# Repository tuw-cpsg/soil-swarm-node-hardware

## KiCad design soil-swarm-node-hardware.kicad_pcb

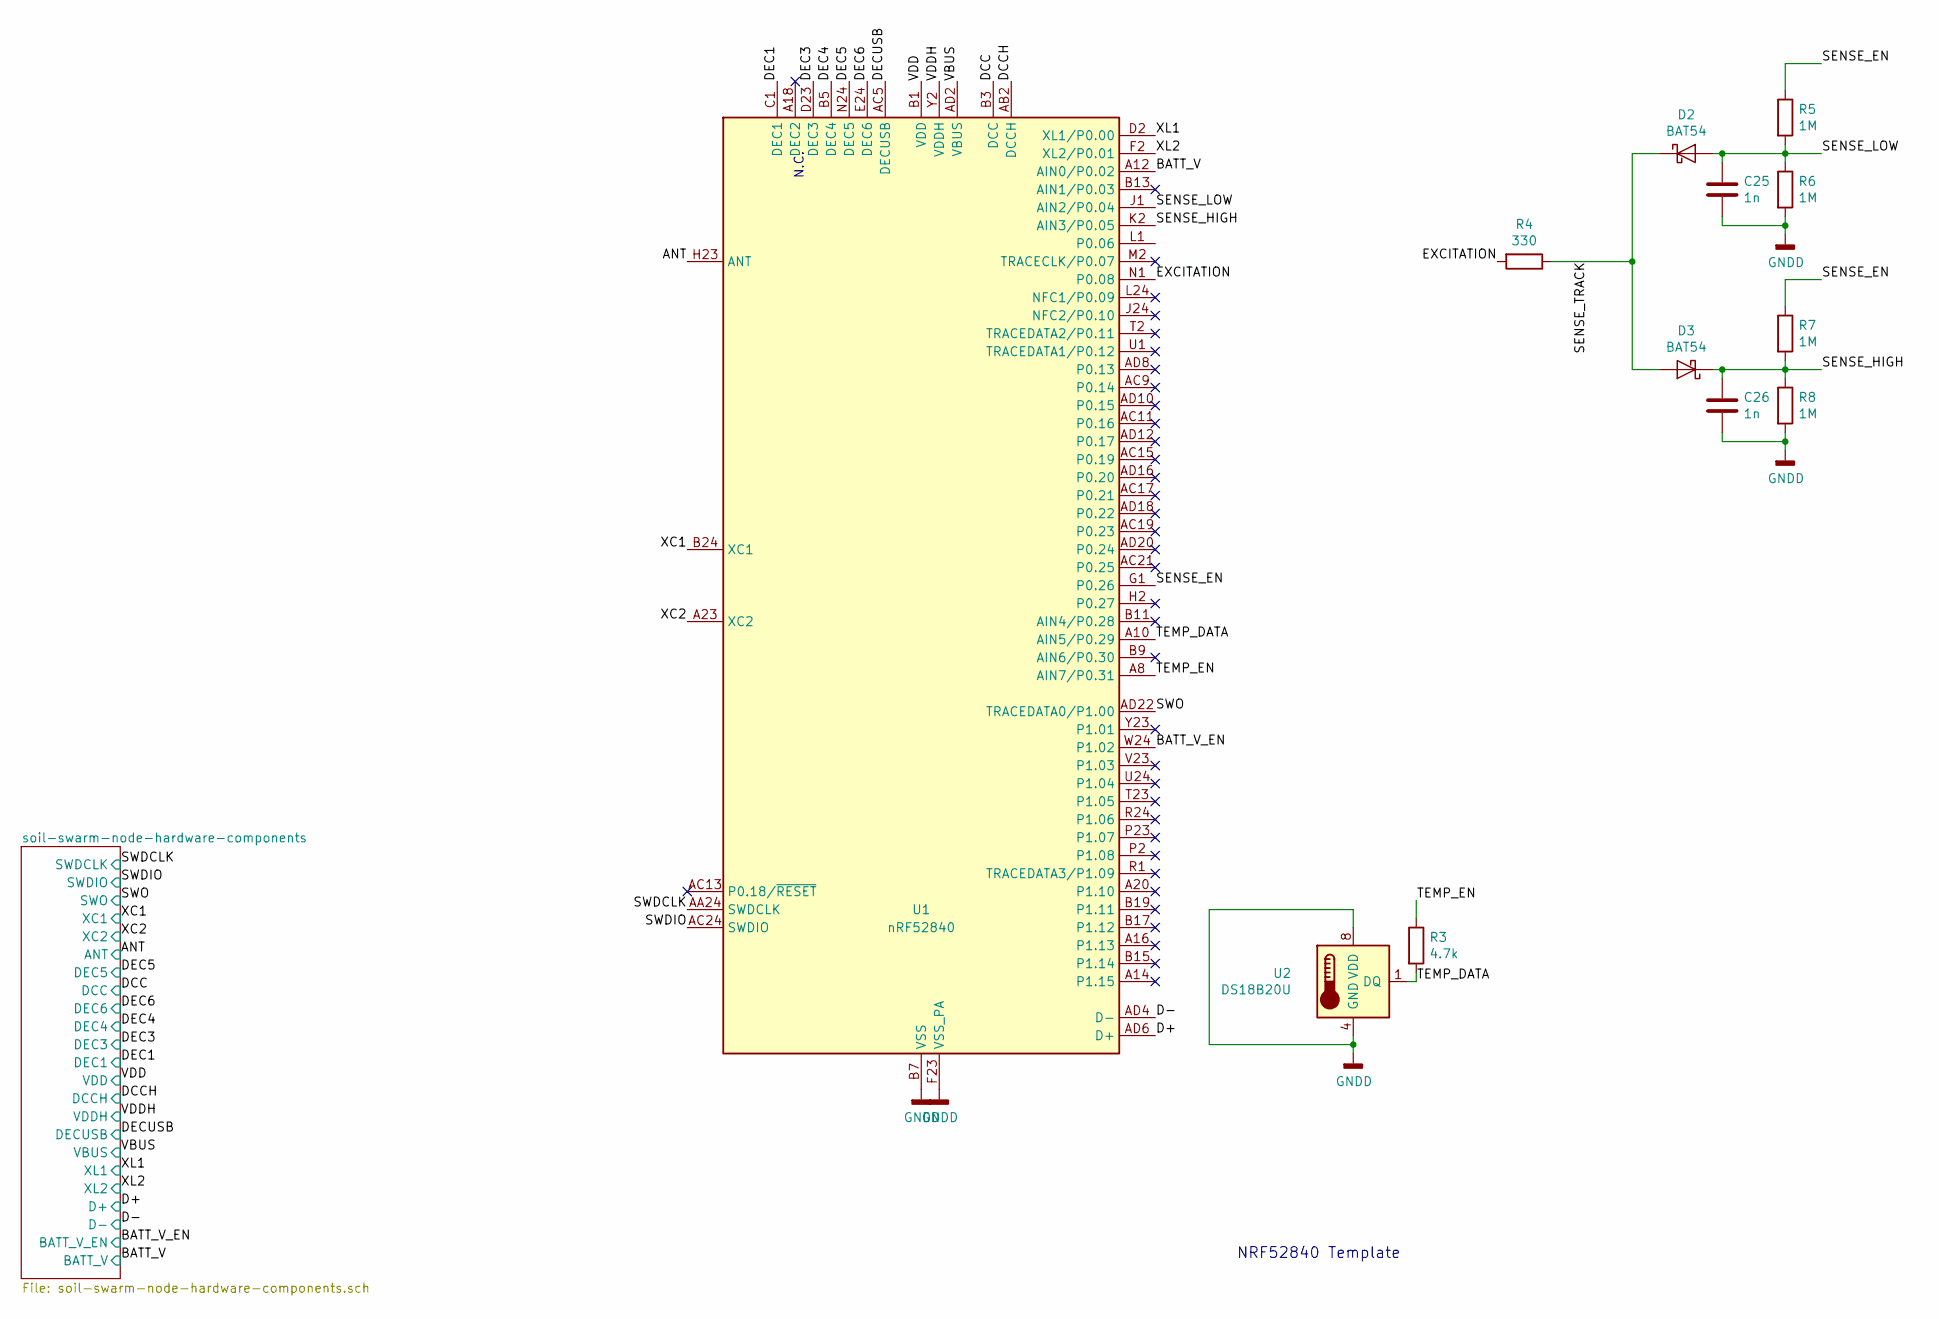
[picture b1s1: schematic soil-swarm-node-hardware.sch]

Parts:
C25, C26: 1n; C_0402_1005Metric
D2, D3: BAT54; D_SOD-323
R3: 4.7k; R_0402_1005Metric
R4: 330; R_0402_1005Metric
R5, R6, R7, R8: 1M; R_0402_1005Metric
U1: nRF52840; Nordic_AQFN-73-1EP_7x7mm_P0.5mm
U2: DS18B20U; MSOP-8_3x3mm_P0.65mm

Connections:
/ANT: U1.H23 (ANT); also elsewhere on the board
/BATT_V: U1.A12 (AIN0/P0.02); also elsewhere on the board
/BATT_V_EN: U1.W24 (P1.02); also elsewhere on the board
/D+: U1.AD6 (D+); also elsewhere on the board
/D-: U1.AD4 (D-); also elsewhere on the board
/DCC: U1.B3 (DCC); also elsewhere on the board
/DCCH: U1.AB2 (DCCH); also elsewhere on the board
/DEC1: U1.C1 (DEC1); also elsewhere on the board
/DEC3: U1.D23 (DEC3); also elsewhere on the board
/DEC4: U1.B5 (DEC4), U1.E24 (DEC6); also elsewhere on the board
/DEC5: U1.N24 (DEC5); also elsewhere on the board
/DECUSB: U1.AC5 (DECUSB); also elsewhere on the board
/EXCITATION: R4.2, U1.N1 (P0.08)
/SENSE_EN: R5.1, R7.1, U1.G1 (P0.26)
/SENSE_HIGH: C26.1, D3.1 (K), R7.2, R8.1, U1.K2 (AIN3/P0.05)
/SENSE_LOW: C25.1, D2.2 (A), R5.2, R6.1, U1.J1 (AIN2/P0.04)
/SENSE_TRACK: D2.1 (K), D3.2 (A), R4.1; also elsewhere on the board
/SWDCLK: U1.AA24 (SWDCLK); also elsewhere on the board
/SWDIO: U1.AC24 (SWDIO); also elsewhere on the board
/SWO: U1.AD22 (TRACEDATA0/P1.00); also elsewhere on the board
/TEMP_DATA: R3.2, U1.A10 (AIN5/P0.29), U2.1 (DQ)
/TEMP_EN: R3.1, U1.A8 (AIN7/P0.31)
/XC1: U1.B24 (XC1); also elsewhere on the board
/XC2: U1.A23 (XC2); also elsewhere on the board
/XL1: U1.D2 (XL1/P0.00); also elsewhere on the board
/XL2: U1.F2 (XL2/P0.01); also elsewhere on the board
GND: C25.2, C26.2, R6.2, R8.2, U1.B7 (VSS), U1.EP (VSS), U1.F23 (VSS_PA), U2.4 (GND), U2.8 (VDD); also elsewhere on the board
LINE: U1.Y2 (VDDH); also elsewhere on the board
VBUS: U1.AD2 (VBUS); also elsewhere on the board
VCC: U1.A22 (VDD), U1.AD14 (VDD), U1.AD23 (VDD), U1.B1 (VDD), U1.W1 (VDD); also elsewhere on the board

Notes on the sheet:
NRF52840 Template
N.C.

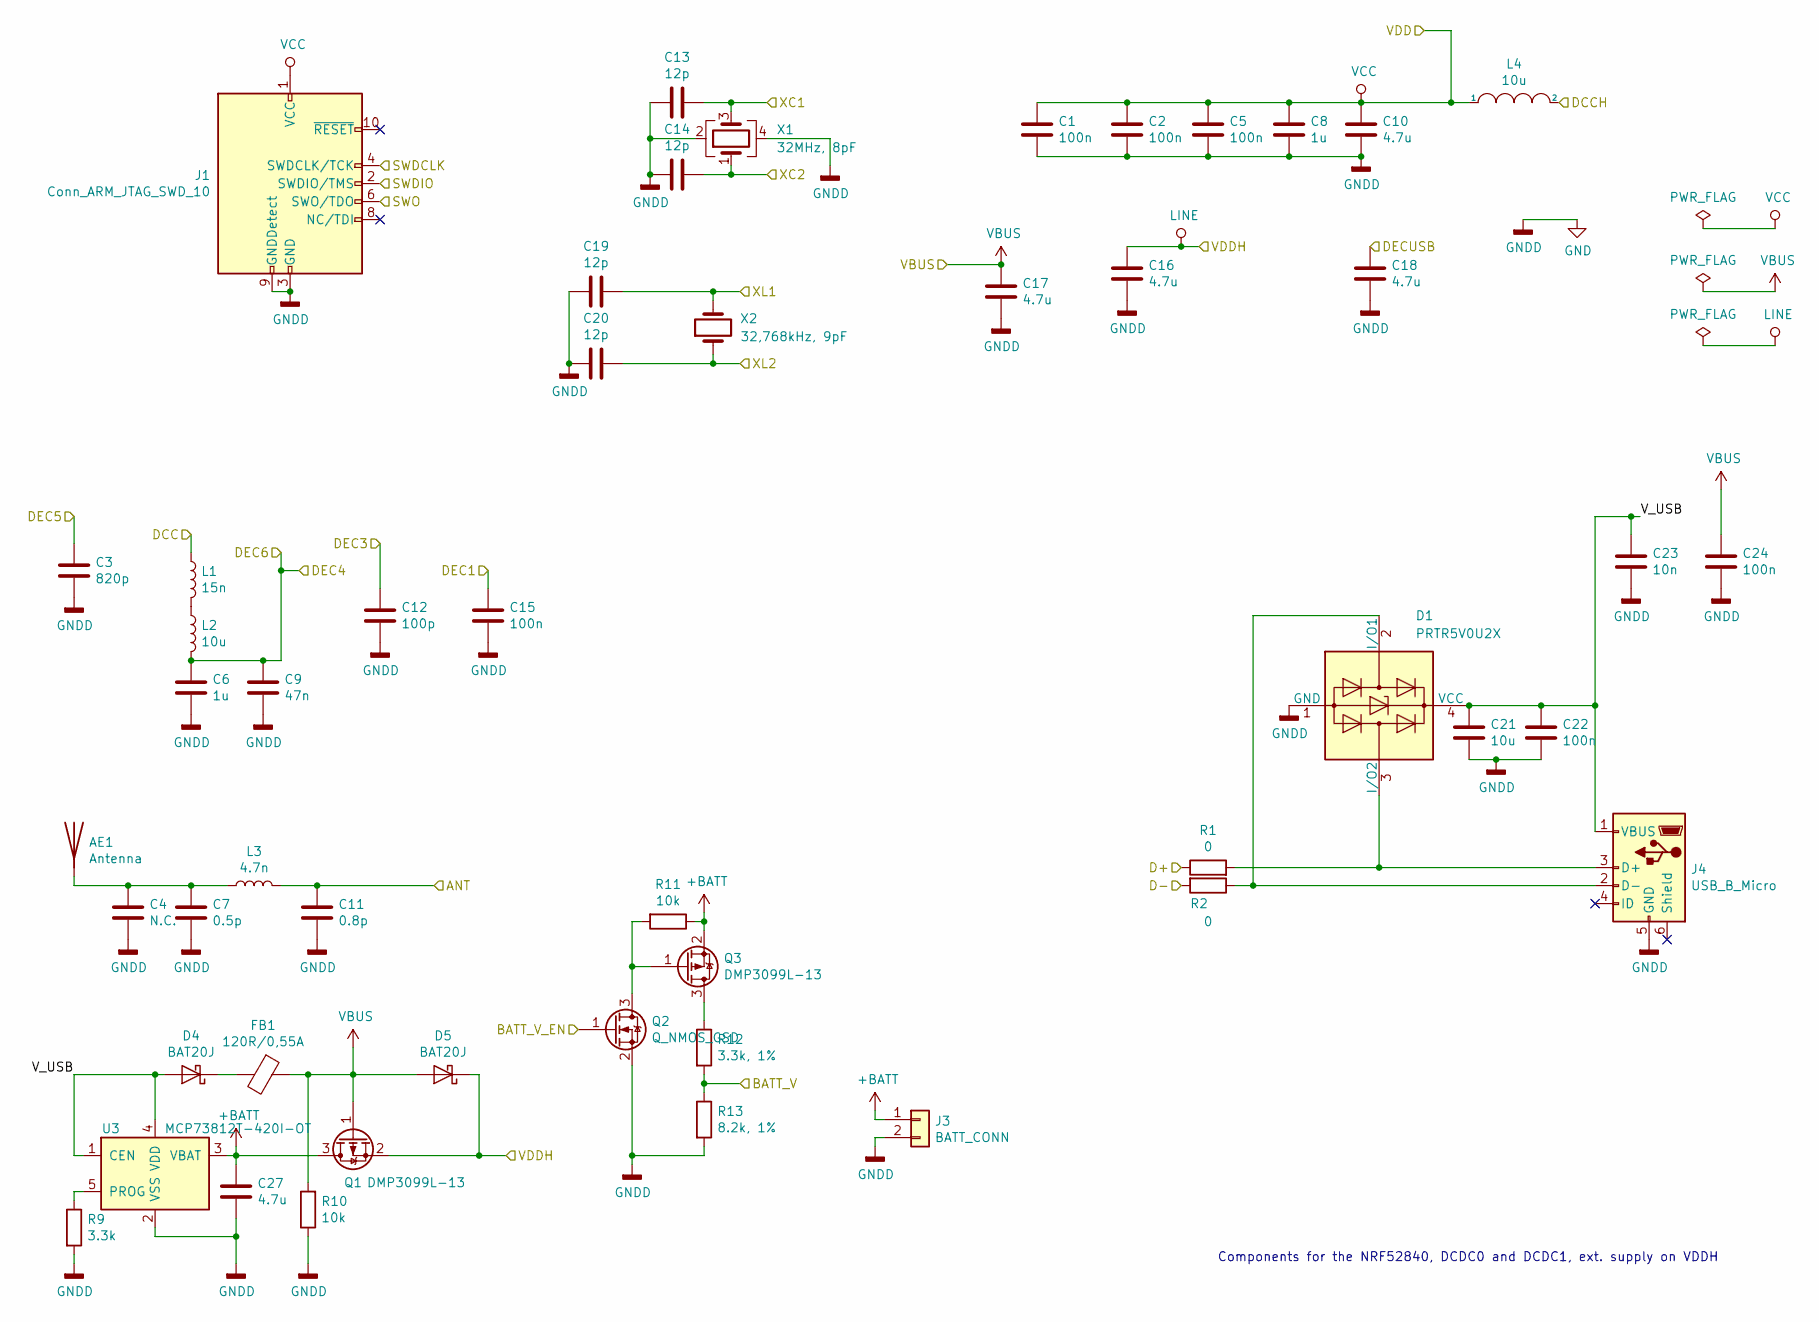
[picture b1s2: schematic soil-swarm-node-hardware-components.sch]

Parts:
AE1: Antenna; Texas_SWRA117D_2.4GHz_Right
C1, C2, C5, C15, C22, C24: 100n; C_0402_1005Metric
C3: 820p; C_0402_1005Metric
C4: N.C.; C_0402_1005Metric
C6, C8: 1u; C_0603_1608Metric
C7: 0.5p; C_0402_1005Metric
C9: 47n; C_0402_1005Metric
C10, C16, C17, C18, C27: 4.7u; C_0603_1608Metric
C11: 0.8p; C_0402_1005Metric
C12: 100p; C_0402_1005Metric
C13, C14, C19, C20: 12p; C_0402_1005Metric
C21: 10u; C_0603_1608Metric
C23: 10n; C_0402_1005Metric
D1: PRTR5V0U2X; SOT-143
D4, D5: BAT20J; D_SOD-323
FB1: 120R/0,55A; L_0402_1005Metric
J1: Conn_ARM_JTAG_SWD_10; PinHeader_2x05_P1.27mm_Vertical_SMD
J3: BATT_CONN; JST_PH_S2B-PH-K_1x02_P2.00mm_Horizontal
J4: USB_B_Micro; USB_Micro-B_Molex_47346-0001
L1: 15n; L_0402_1005Metric
L2, L4: 10u; L_0603_1608Metric
L3: 4.7n; L_0402_1005Metric
Q1, Q3: DMP3099L-13; SOT-23
Q2: Q_NMOS_GSD; SOT-23
R1, R2: 0; R_0402_1005Metric
R9: 3.3k; R_0402_1005Metric
R10, R11: 10k; R_0402_1005Metric
R12: 3.3k, 1%; R_0402_1005Metric
R13: 8.2k, 1%; R_0402_1005Metric
U3: MCP73812T-420I-OT; SOT-23-5
X1: 32MHz, 8pF; Crystal_SMD_2016-4Pin_2.0x1.6mm
X2: 32,768kHz, 9pF; Crystal_SMD_3215-2Pin_3.2x1.5mm

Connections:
+BATT: C27.1, J3.1, Q1.3 (D), Q3.2 (S), R11.1, U3.3 (VBAT)
/ANT: C11.1, L3.2; also elsewhere on the board
/BATT_V: R12.2, R13.1; also elsewhere on the board
/BATT_V_EN: Q2.1 (G); also elsewhere on the board
/D+: R1.1; also elsewhere on the board
/D-: R2.2; also elsewhere on the board
/DCC: L1.1; also elsewhere on the board
/DCCH: L4.2; also elsewhere on the board
/DEC1: C15.1; also elsewhere on the board
/DEC3: C12.1; also elsewhere on the board
/DEC4: C6.1, C9.1, L2.2; also elsewhere on the board
/DEC5: C3.1; also elsewhere on the board
/DECUSB: C18.1; also elsewhere on the board
/SWDCLK: J1.4 (SWDCLK/TCK); also elsewhere on the board
/SWDIO: J1.2 (SWDIO/TMS); also elsewhere on the board
/SWO: J1.6 (SWO/TDO); also elsewhere on the board
/XC1: C13.2, X1.3; also elsewhere on the board
/XC2: C14.2, X1.1; also elsewhere on the board
/XL1: C19.2, X2.2; also elsewhere on the board
/XL2: C20.2, X2.1; also elsewhere on the board
/soil-swarm-node-hardware-components/V_USB: C21.1, C22.1, C23.1, D1.4 (VCC), D4.2 (A), J4.1 (VBUS), U3.1 (CEN), U3.4 (VDD)
GND: AE1.2, C1.2, C2.2, C3.2, C4.2, C5.2, C6.2, C7.2, C8.2, C9.2, C10.2, C11.2, C12.2, C13.1, C14.1, C15.2, C16.2, C17.2, C18.2, C19.1, C20.1, C21.2, C22.2, C23.2, C24.2, C27.2, D1.1 (GND), J1.3 (GND), J1.5 (GND), J1.9 (GNDDetect), J3.2, J4.5 (GND), Q2.2 (S), R9.2, R10.1, R13.2, U3.2 (VSS), X1.2, X1.4; also elsewhere on the board
LINE: C16.1, D5.1 (K), Q1.2 (S); also elsewhere on the board
unnamed: AE1.1, C4.1, C7.1, L3.1
unnamed: D1.2 (I/O1), J4.2 (D-), R2.1
unnamed: D1.3 (I/O2), J4.3 (D+), R1.2
unnamed: D4.1 (K), FB1.2
unnamed: L1.2, L2.1
unnamed: Q2.3 (D), Q3.1 (G), R11.2
unnamed: Q3.3 (D), R12.1
unnamed: R9.1, U3.5 (PROG)
VBUS: C17.1, C24.1, D5.2 (A), FB1.1, Q1.1 (G), R10.2; also elsewhere on the board
VCC: C1.1, C2.1, C5.1, C8.1, C10.1, J1.1 (VCC), L4.1; also elsewhere on the board

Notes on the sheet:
Components for the NRF52840, DCDC0 and DCDC1, ext. supply on VDDH

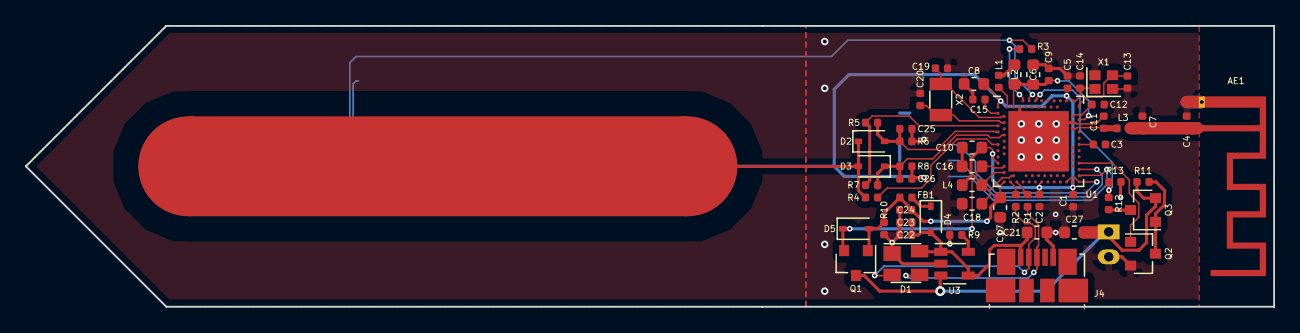
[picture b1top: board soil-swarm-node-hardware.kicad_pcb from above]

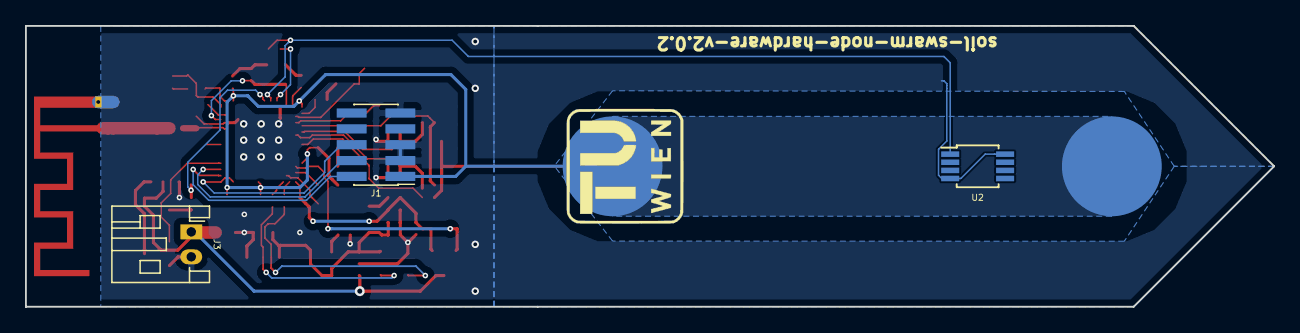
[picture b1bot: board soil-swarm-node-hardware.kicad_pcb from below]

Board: 2 copper layers, 100.0 x 22.5 mm, 64 parts (4 on the bottom side), 40 nets.

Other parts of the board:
C***: SENSE; c_layout_2
C***#2: SENSE; c_layout_1

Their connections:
/SENSE_TRACK: C***#2.1; also elsewhere on the board
VCC: C***.1; also elsewhere on the board

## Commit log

2019-06-24 update documentation
2019-06-27 create new version based on nRF52840
2019-07-05 finalizing 2.0.0
2019-08-29 update based on Nordic specification
2019-11-04 C11 GND only via F23
2020-04-08 update schematic
